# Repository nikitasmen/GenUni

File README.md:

# University Studies Archive

## Overview
This repository contains a comprehensive collection of projects, exercises, assignments, and study materials from my university education. It serves as a portfolio of my academic work across various disciplines including computer science, mathematics, and electronics.

## Repository Structure

### 📁 Coding
Collection of programming projects and exercises across various languages and paradigms:

- **Algorithms**: Implementation of various algorithms and problem-solving approaches
- **CodeSculptor**: Python projects including interactive games with visual elements
- **Computer Architecture**: Low-level programming and hardware interface exercises
- **CUDA C**: Parallel programming using NVIDIA's CUDA platform
- **Data Structures**: Implementation of various data structures
- **Linux Base**: Linux system administration and shell scripting
- **Microcontrollers**: Projects involving embedded systems programming
- **OOP Exercises**: Object-oriented programming concepts and implementations
- **Web Development**: 
  - **E-lib**: Online library management system
  - **Something-like-ebay**: E-commerce platform implementation
  - **Forum**: Online discussion platform with database integration

### 📁 General
Reference materials and academic resources:

- **Books**: Technical literature including compiler design and development handbooks
- **Collected**: Presentations and reference documents (e.g., Git & GitHub materials)
- **Papers**: Academic papers and research publications

### 📁 Math
Mathematical coursework and assignments:

- **Analog & Digital Control**: Control systems theory and implementation
- **Discrete Mathematics**: Foundations of mathematical structures
- **Signal & Image Processing**: Analysis and manipulation of signals and images
- **Signals & Systems**: Systems theory and signal analysis

### 📁 Electronics
Hardware-focused projects and laboratory work:

- **BJT Test**: Transistor testing and characterization
- **KiCad**: Electronic circuit design projects
- **Measurements**: Electronic measurement techniques and data
- **Op-Amp Tester**: Operational amplifier testing projects
- **Organic Electronics**: Work related to organic electronic components

## Highlighted Projects

- **Paragraph Formatting Checker**: Python utility for validating text formatting in English and Greek
- **Asteroids Game**: Interactive game implemented using Python and SimpleGUI
- **E-commerce Database**: Complete SQL implementation for an online marketplace
- **E-library System**: Web-based library management with PHP backend

## Technologies

This repository demonstrates proficiency in:

- **Programming Languages**: Python, C/C++, PHP, SQL, JavaScript
- **Web Technologies**: Frontend and backend web development
- **Database Systems**: SQL database design and management
- **Electronics**: Circuit design and testing
- **Mathematical Modeling**: Control systems and signal processing

## License

This repository is primarily for personal and educational use. Please respect the academic integrity policies of educational institutions if referencing this work.

---

*Note: This repository represents academic work completed during my university studies and serves as a portfolio of my learning journey across multiple disciplines.*

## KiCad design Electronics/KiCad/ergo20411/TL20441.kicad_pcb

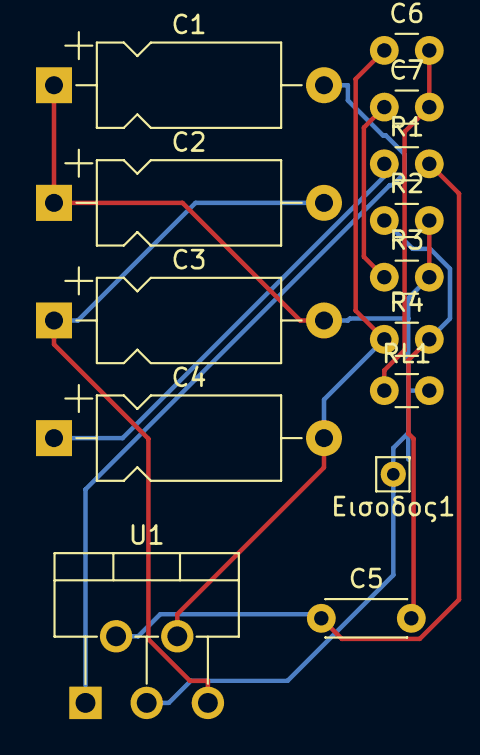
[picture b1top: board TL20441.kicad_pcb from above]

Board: 2 copper layers, 14 parts (0 on the bottom side), 9 nets.

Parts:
C1: 1 uF; CP_Axial_L10.0mm_D4.5mm_P15.00mm_Horizontal
C2: 100 uF; CP_Axial_L10.0mm_D4.5mm_P15.00mm_Horizontal
C3: 0.01 uF; CP_Axial_L10.0mm_D4.5mm_P15.00mm_Horizontal
C4: 0.047 uF; CP_Axial_L10.0mm_D4.5mm_P15.00mm_Horizontal
C5: 470 uF; C_Disc_D4.3mm_W1.9mm_P5.00mm
C6: 1000 uF; C_Disc_D3.0mm_W1.6mm_P2.50mm
C7: 0.1 uF; C_Disc_D3.0mm_W1.6mm_P2.50mm
R1: 47 Ω; C_Disc_D3.0mm_W1.6mm_P2.50mm
R2: 2.2 Ω; C_Disc_D3.0mm_W1.6mm_P2.50mm
R3: 1 Ω; C_Disc_D3.0mm_W1.6mm_P2.50mm
R4: 220 Ω; C_Disc_D3.0mm_W1.6mm_P2.50mm
RL1: 8 ohm; C_Disc_D3.0mm_W1.6mm_P2.50mm
U1: TDA2003; TO-220-5_P3.4x3.7mm_StaggerOdd_Lead3.8mm_Vertical
Εισοδος1: 20W; Pin_D0.7mm_L6.5mm_W1.8mm_FlatFork

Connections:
+ Vcc 12v: C2.2, C3.1, U1.5 (V+)
GNDREF: C1.1, C2.1, C3.2, R2.2, R3.2, RL1.2, U1.3 (GND), Εισοδος1.1
unnamed: C4.1, R1.1
unnamed: C4.2, C6.1, R4.1, U1.4
unnamed: C5.2, R2.1, R4.2
unnamed: C6.2, C7.2, RL1.1
unnamed: C7.1, R3.1
unnamed: C1.2, U1.1 (+)
unnamed: C5.1, R1.2, U1.2 (-)

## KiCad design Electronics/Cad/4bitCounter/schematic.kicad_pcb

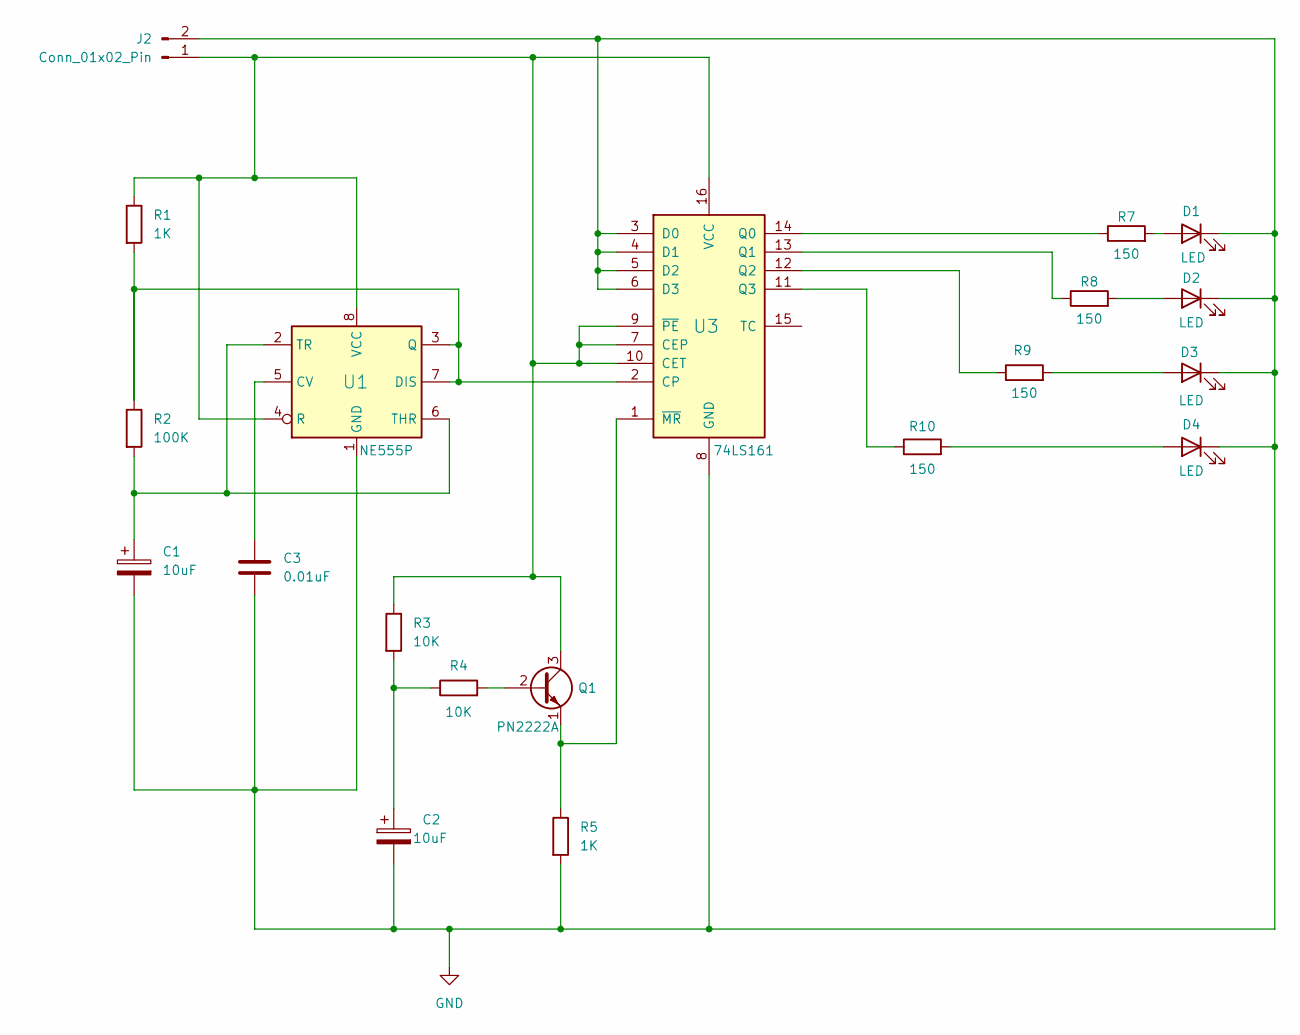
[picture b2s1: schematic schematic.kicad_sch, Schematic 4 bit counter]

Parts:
C1, C2: 10uF; Capacitor
C3: 0.01uF; Capacitor
D1, D2, D3, D4: LED
J2: Conn_01x02_Pin; Connector
Q1: PN2222A; Transistor
R1, R5: 1K; Resistor
R2: 100K; Resistor
R3, R4: 10K; Resistor
R7, R8, R9, R10: 150; Resistor
U1: NE555P; Timer
U3: 74LS161; CounterChip

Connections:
GND: C1.2, C2.2, C3.2, D1.1 (K), D2.1 (K), D3.1 (K), D4.1 (K), J2.2, R5.2, U1.1 (GND), U3.3 (D0), U3.4 (D1), U3.5 (D2), U3.6 (D3), U3.8 (GND)
unnamed: C2.1, R3.2, R4.1
unnamed: D1.2 (A), R7.2
unnamed: D2.2 (A), R8.2
unnamed: D3.2 (A), R9.2
unnamed: D4.2 (A), R10.2
unnamed: J2.1, Q1.3 (C), R1.1, R3.1, U1.4 (R), U1.8 (VCC), U3.7 (CEP), U3.9 (~PE), U3.10 (CET), U3.16 (VCC)
unnamed: Q1.2 (B), R4.2
unnamed: Q1.1 (E), R5.1, U3.1 (~MR)
unnamed: C3.1, U1.5 (CV)
unnamed: R1.2, R2.1, U1.3 (Q), U1.7 (DIS), U3.2 (CP)
unnamed: C1.1, R2.2, U1.2 (TR), U1.6 (THR)
unnamed: R7.1, U3.14 (Q0)
unnamed: R8.1, U3.13 (Q1)
unnamed: R9.1, U3.12 (Q2)
unnamed: R10.1, U3.11 (Q3)

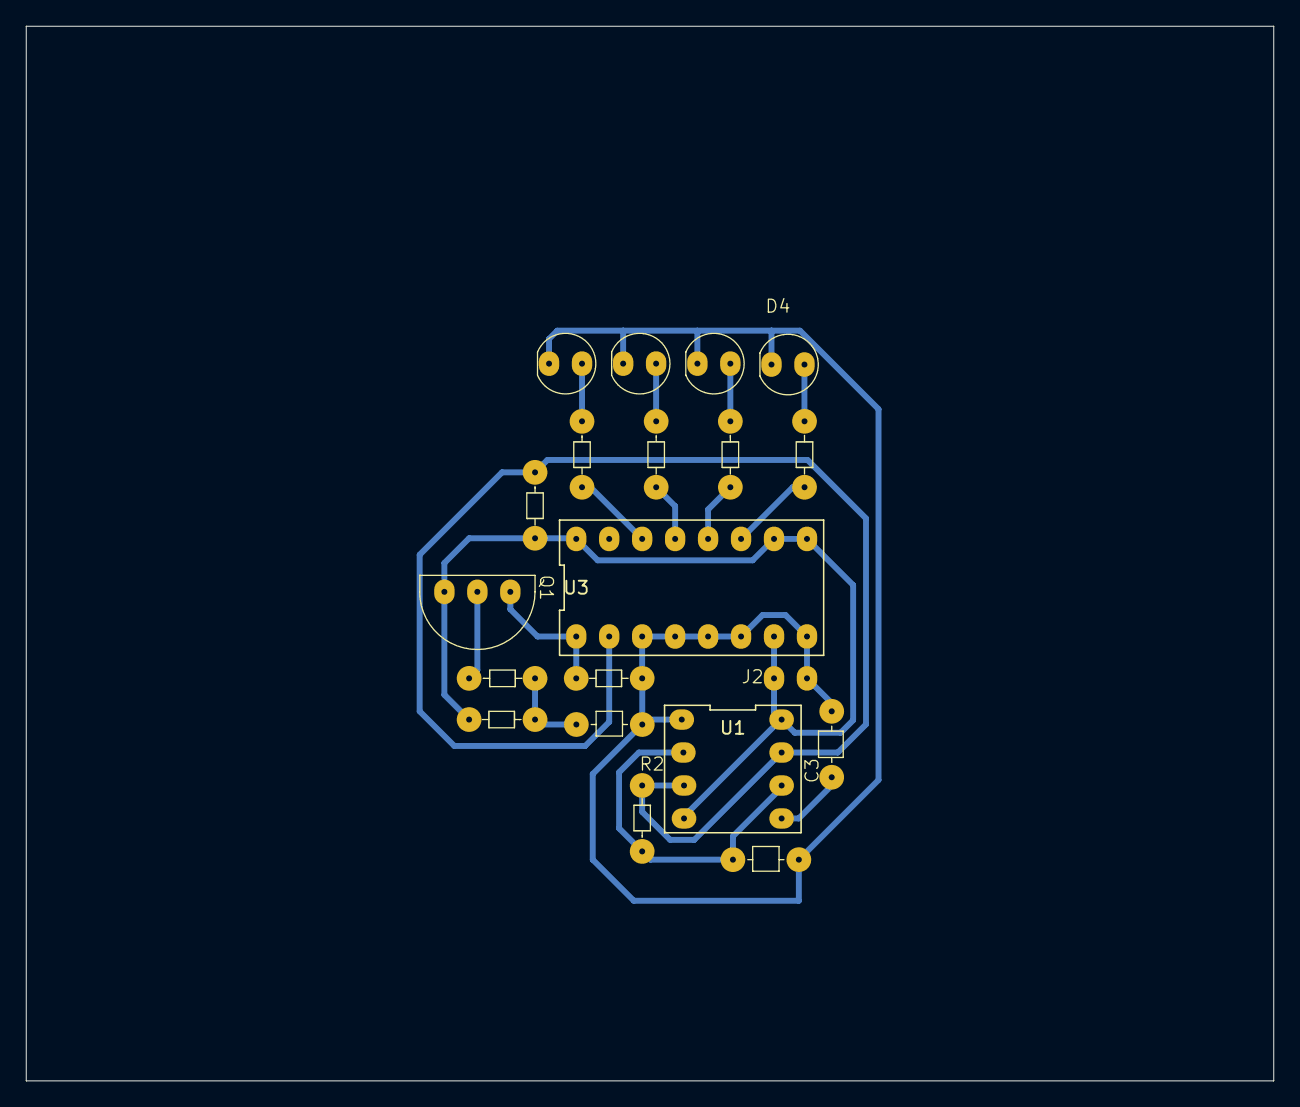
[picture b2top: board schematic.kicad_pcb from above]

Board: 2 copper layers, 96.1 x 81.3 mm, 20 parts (0 on the bottom side), 16 nets.

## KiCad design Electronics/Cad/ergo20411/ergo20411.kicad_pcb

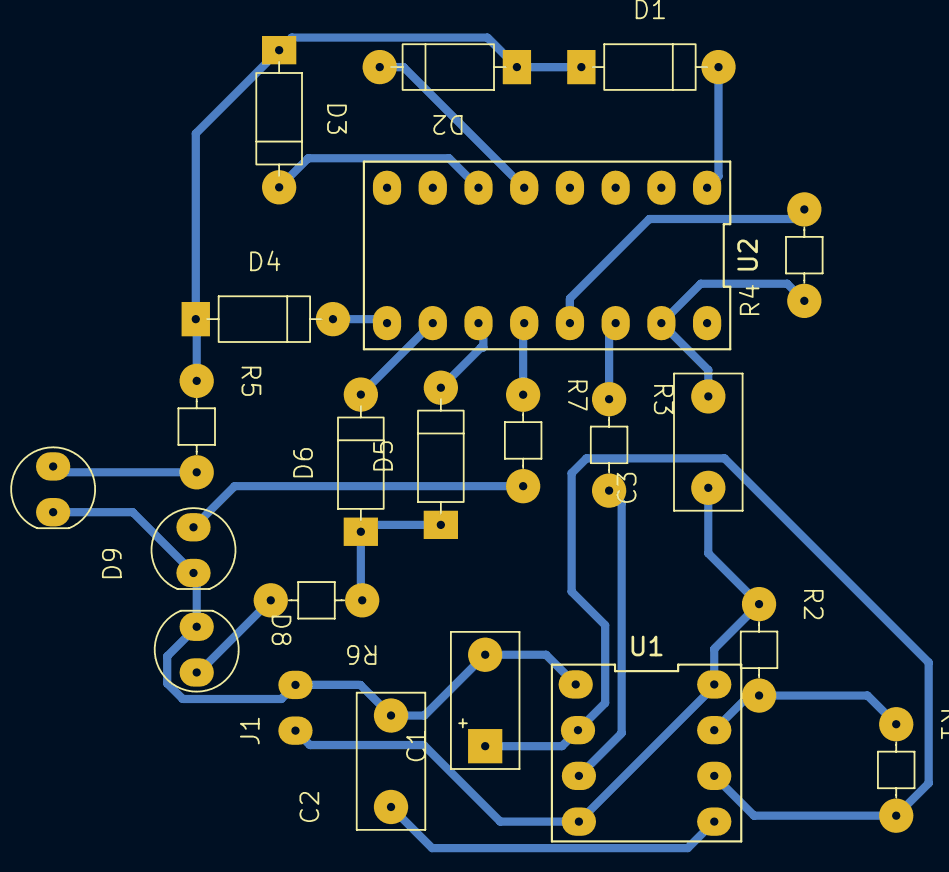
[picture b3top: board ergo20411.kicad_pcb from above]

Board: 2 copper layers, 22 parts (0 on the bottom side), 21 nets.

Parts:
C1: 47u; CP
C2: 0.01uF; Capacitor
C3: 6.8nF; Capacitor
D1, D2, D3, D4, D5, D6: 1N4148; Diode
D7: LED-GREEN; LED
D8: LED-YELLOW; LED
D9: LED-RED; LED
J1: Conn_01x02_Pin; Connector
R1, R3: 10k; Resistor
R2: 22k; Resistor
R4: 100k; Resistor
R5, R6, R7: 100R; Resistor
U1: LM555xN; 555
U2: 4017; Counter

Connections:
GND: C1.2, C2.2, D7.1 (K), D8.1 (K), D9.1 (K), J1.2, U1.1 (GND)
unnamed: D1.2 (A), U2.1 (Q5)
unnamed: D1.1 (K), D2.1 (K), D3.1 (K), D4.1 (K), R5.1
unnamed: D2.2 (A), U2.5 (Q6)
unnamed: D3.2 (A), U2.6 (Q7)
unnamed: D4.2 (A), U2.9 (Q8)
unnamed: D5.2 (A), U2.11 (Q9)
unnamed: D5.1 (K), D6.1 (K), R6.1
unnamed: D6.2 (A), U2.10 (Q4)
unnamed: D7.2 (A), R5.2
unnamed: D8.2 (A), R6.2
unnamed: D9.2 (A), R7.2
unnamed: C3.1, J1.1, R2.1, U1.4 (R), U1.8 (VCC)
unnamed: C2.1, U1.5 (CV)
unnamed: R1.1, R2.2, U1.7 (DIS)
unnamed: R3.2, U1.3 (Q)
unnamed: C1.1, R1.2, U1.2 (TR), U1.6 (THR)
unnamed: R4.2, U2.13 (CKEN)
unnamed: R3.1, U2.14 (CLK)
unnamed: R7.1, U2.12 (Cout)
unnamed: C3.2, R4.1, U2.15 (Reset)

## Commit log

2024-12-01 Initial
2024-12-02 Updates in webuni
2024-12-03 Update Kicad
2024-12-08 Update file managment
2024-12-08 Initial ask2_1 mpikakis
2024-12-08 inial ask2_2
2024-12-10 Update webUni
2024-12-14 Update codeskultor
2024-12-15 update 4bit counter
2024-12-17 Update 4bitcounter
2024-12-20 Update counter
2025-01-03 Update on kicad project
2025-01-03 Change folder
2025-01-03 Update 2nd pack of excersizes
2025-01-08 Updates on kicad
2025-01-08 Update pcb
2025-01-16 Major update
2025-01-16 Add Kicad project
2025-01-16 Add cuda c init && carDb
2025-01-16 Add stuff
2025-01-19 Update kicad project
2025-01-22 Update carDb
2025-01-22 Updates webUni
2025-01-22 Clean up
2025-01-22 Update codeSculptor
2025-01-22 Update path codesculptor
2025-01-22 Update paths, add book
2025-01-24 Update hangman
2025-01-25 Remove ds store
2025-01-25 Minor review
2025-01-31 Add new files for sorting algorithm steps and search function implementation
2025-02-06 Update e-lib
2025-02-12 renaming
2025-02-12 remove vhdl
2025-02-14 Add new book
2025-02-23 Add report lab01 progLang
2025-02-24 Add .gitignore to exclude .DS_Store and .vscode files
2025-02-25 Add new algorithms and exercises for weeks 00 to 03, including sorting and random number generation
2025-02-25 Add new assembly and document files for architecture exercises
2025-02-25 Add new lab documents for anaf and paradoteo exercises
2025-02-25 Add new MATLAB scripts for signal processing exercises, including delta functions, Laplace transforms, and convolution
2025-02-25 Add new ZIP and PDF files for various exercises and lectures in signal processing
2025-02-25 Add new PDF documents and MATLAB scripts for analog and digital control exercises
2025-02-25 Add new CAD PDF document and remove KiCad subproject
2025-02-25 Add metrisis docx's and pdf's
2025-02-25 Add microControllers lesson stuff
2025-02-26 Add qa-automation-istqb-exam
2025-02-28 Add initial dino game
2025-03-11 add theoreticsl excersize
2025-03-11 Update subproject reference for E-Lib
2025-03-11 Reinstall kicad
2025-03-13 Add lab01 solutions discrete math
2025-03-14 Update paths and add lab excersize
2025-03-14 Update organics lab01 path and add lab's excersize
2025-03-15 Add compiler design book
2025-03-15 Extract excersize
2025-03-25 Add lab02 excersize
2025-03-25 Add paragraph validation checks with regex in lab_02.py
2025-03-25 Improve Greek sentence validation regex in lab_02.py and restore commented code for number checking
2025-03-25 Refine regex patterns for sentence validation in lab_02.py to improve accuracy and support Greek punctuation
2025-03-25 Refactor ParagraphCheck methods to use instance variables and improve input handling
2025-03-29 Refactor ParagraphCheck class to initialize instance variables and streamline input handling for multiple paragraph checks
2025-03-29 refactor(regex):update regex for greek question mark
2025-03-29 add forum web progamming project
2025-03-30 Same exercise different solution
2025-03-30 Refactor ParagraphCheck class to use a dictionary for checks and streamline input handling
2025-03-30 Enhance ParagraphCheck class to format and display results of paragraph checks
2025-03-30 Remove obsolete subproject directory for the forum web programming project
2025-04-13 Add book for testing
2025-04-28 Remove obsolete E-lib submodule and update submodule commit for 406-db-major-project
2025-04-28 Add e-lib project weDevelpment Course
2025-04-30 Add cpp excersize
2025-05-05 Add README.md to document university studies archive and project structure
2025-05-08 remover obsolete project(repo)
2025-05-08 Add swl project
2025-05-16 Add initial project ptx and xlsx
2025-05-16 Add initial tictactoe
2025-05-18 Add various programming and testing books in PDF format
    - Added "Visual Basic C++ 6.pdf" to the Programming Languages section.
    - Added "Visual C++ for Dummies Quick Reference.pdf" to the Programming Languages section.
    - Added "C Programming Language.pdf" (with non-ASCII characters in the filename) to the Programming Languages section.
    - Added "C Programming Language_C.pdf" (with non-ASCII characters in the filename) to the Programming Languages section.
    - Added "Foundations of Software Testing - ISTQB Certification Book.pdf" to the Testing section.
    - Added "staqtpsn.pdf" to the Testing section.
2025-05-18 Add new books
2025-05-18 Remove obsolete database and SQL files for the forum project
2025-05-21 Add book
2025-05-22 Add initial statechart lab03
2025-05-22 Refactor state transitions in statechart to improve flow between delayBeforeStop, stopping, standby, and recovering states
2025-05-22 Update statechart: add track command, refine actions in tracking and stopping states, and remove recovering state
2025-05-22 Update statechart: rename track command to trackMotion and adjust actions in scanning and tracking states
2025-05-22 Update statechart: change batteryCritical transitions to recovery state and remove standby state
2025-05-23 Update statechart: remove stopScan command, rename enterStandby and exitStandby to standby in commands, and adjust recovery actions
2025-05-23 Add oop project implementetion
2025-05-30 Add initial statemachine grammar definition
2025-05-30 Add calculation operator definition to statemachine grammar
2025-05-30 Refactor statemachine grammar to correct calculation section and update variable definition
2025-05-30 Update values
2025-06-08 Add db project python
2025-06-08 Update project db
2025-06-08 Update more books
2025-06-20 Add Exam2024 June PDF to discrete math resources
2025-06-20 Update elib
2025-06-24 Add new course questions set
2025-07-01 chore(books):Reorder books
